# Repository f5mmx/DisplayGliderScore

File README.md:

Programme de gestion d'afficheur GliderScore
--------------------------------------------
Le but de ce dossier est de fournir les elements necessaires pour la réalisation d'un afficheur a brancher en sortie d'un PC avec GliderScore.

3 modules :
- 1 module de transmission en 2.4Ghz Canal 0 avec display Oled - Receive_Big
- 1 module de reception en 2.4 Ghz Canal 0 pour gestion GRAND afficheur segment diplay 7 digit - Transmit_all
_ 1 module de recpetion en 2.4 Ghz Canal 0 sur chrono avec afficheur Nokia 5119 - Small_Chrono

le Harware est basé sur des modules arduino nano + nrf24l01 + Large Driver 7 digit 

https://www.sparkfun.com/products/13279

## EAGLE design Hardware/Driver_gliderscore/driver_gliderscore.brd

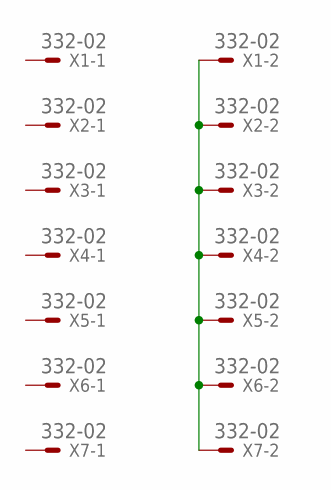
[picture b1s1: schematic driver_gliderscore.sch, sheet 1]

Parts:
X1, X2, X3, X4, X5, X6, X7: 332-02

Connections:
unnamed: X1.2, X2.2, X3.2, X4.2, X5.2, X6.2, X7.2

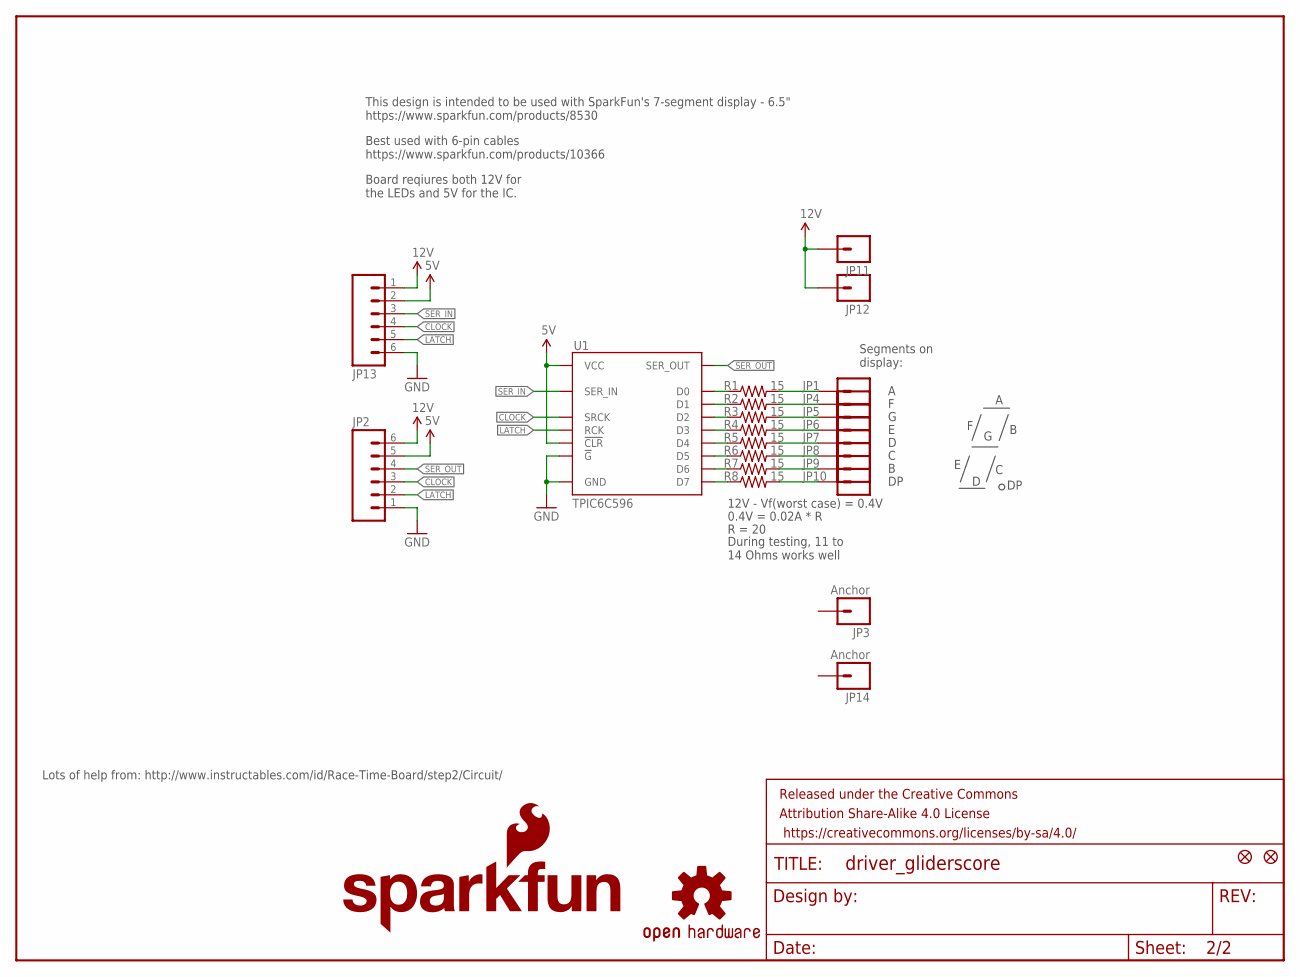
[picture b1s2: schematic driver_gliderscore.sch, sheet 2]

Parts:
FID1, FID2: FIDUCIAL1X2; FIDUCIAL-1X2
FRAME1: FRAME-LETTER; CREATIVE_COMMONS
JP1, JP4, JP5, JP6, JP7, JP8, JP9, JP10, JP11, JP12: M01PTH_LONGPAD; 1X01_LONGPAD
JP2, JP13: M06SMD; 1X06-SMD
JP3, JP14: Anchor; 1X01_LONGPAD
LOGO1: SFE_LOGO_NAME_FLAME.1_INCH; SFE_LOGO_NAME_FLAME_.1
LOGO2: OSHW-LOGOS; OSHW-LOGO-S
R1, R2, R3, R4, R5, R6, R7, R8: 15; 0603-RES
U1: TPIC6C596; SO016

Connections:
5V: JP2.5, JP13.2, U1.1 (VCC), U1.7 (!CLR)
12V: JP2.6, JP11.1, JP12.1, JP13.1
CLOCK: JP2.3, JP13.4, U1.15 (SRCK)
D0: R1.1, U1.3 (D0)
D1: R2.1, U1.4 (D1)
D2: R3.1, U1.5 (D2)
D3: R4.1, U1.6 (D3)
D4: R5.1, U1.11 (D4)
D5: R6.1, U1.12 (D5)
D6: R7.1, U1.13 (D6)
D7: R8.1, U1.14 (D7)
GND: JP2.1, JP13.6, U1.8 (!G), U1.16 (GND)
LATCH: JP2.2, JP13.5, U1.10 (RCK)
S0: JP1.1, R1.2
S1: JP4.1, R2.2
S2: JP5.1, R3.2
S3: JP6.1, R4.2
S4: JP7.1, R5.2
S5: JP8.1, R6.2
S6: JP9.1, R7.2
S7: JP10.1, R8.2
SER_IN: JP13.3, U1.2 (SER_IN)
SER_OUT: JP2.4, U1.9 (SER_OUT)

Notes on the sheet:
Lots of help from: http://www.instructables.com/id/Race-Time-Board/step2/Circuit/
Segments on display:
12V - Vf(worst case) = 0.4V
0.4V = 0.02A * R
R = 20
This design is intended to be used with SparkFun's 7-segment display - 6.5" https://www.sparkfun.com/products/8530
During testing, 11 to 14 Ohms works well
Best used with 6-pin cables https://www.sparkfun.com/products/10366
Board reqiures both 12V for the LEDs and 5V for the IC.

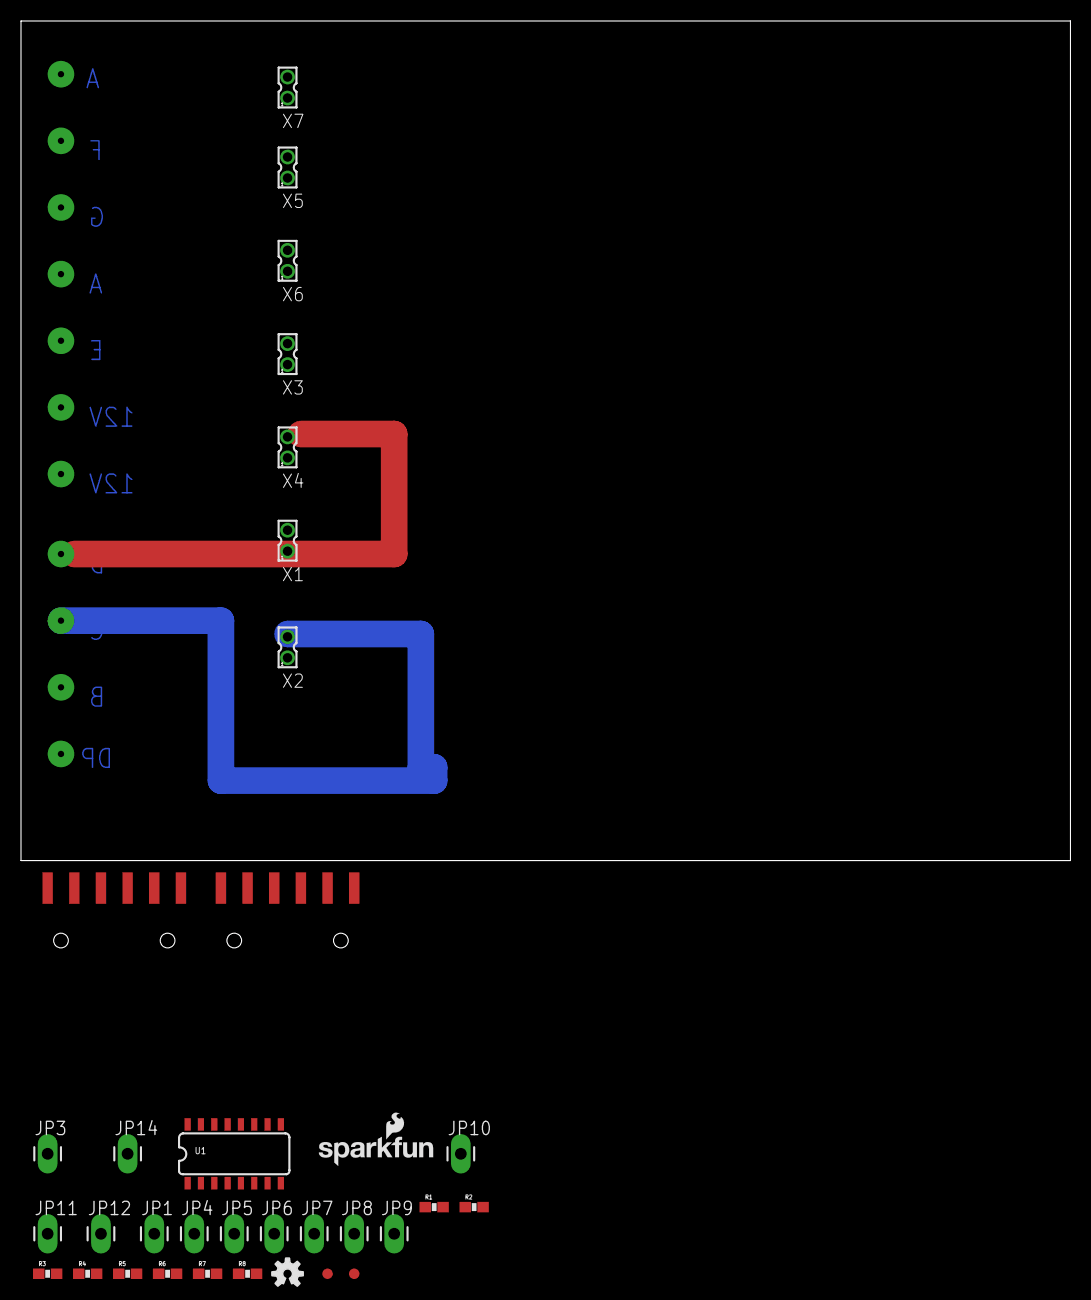
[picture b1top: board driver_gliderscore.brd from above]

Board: 2 copper layers, 100.0 x 80.0 mm, 35 parts (0 on the bottom side), 24 nets.

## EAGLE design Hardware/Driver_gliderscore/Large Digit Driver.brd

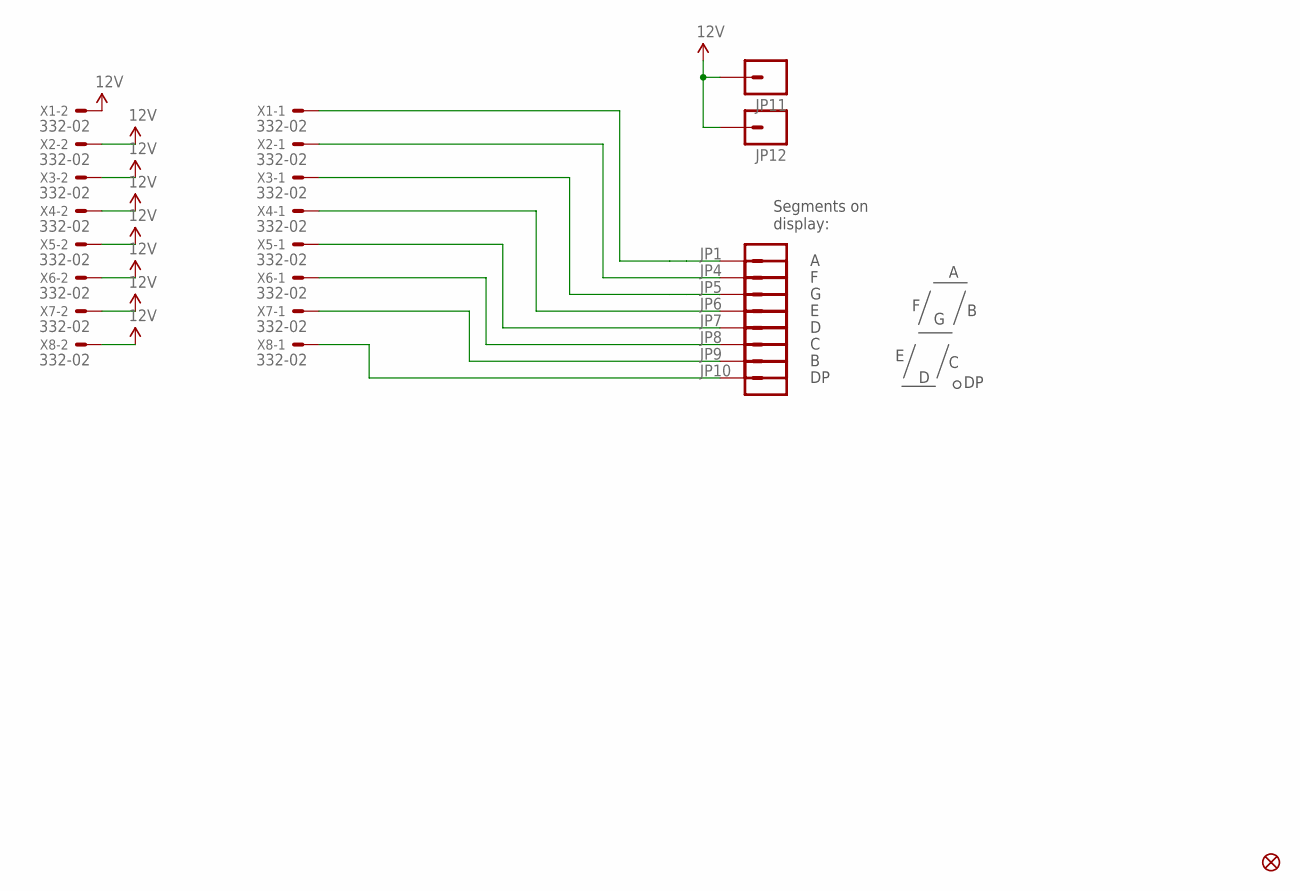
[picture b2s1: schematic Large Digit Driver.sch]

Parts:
FID2: FIDUCIAL1X2; FIDUCIAL-1X2
JP1, JP4, JP5, JP6, JP7, JP8, JP9, JP10, JP11, JP12: M01PTH_LONGPAD; 1X01_LONGPAD
X1, X2, X3, X4, X5, X6, X7, X8: 332-02

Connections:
12V: JP11.1, JP12.1, X1.2, X2.2, X3.2, X4.2, X5.2, X6.2, X7.2, X8.2
unnamed: JP9.1, X7.1
S0: JP1.1, X1.1
S1: JP4.1, X2.1
S2: JP5.1, X3.1
S3: JP6.1, X4.1
S4: JP7.1, X5.1
S5: JP8.1, X6.1
S7: JP10.1, X8.1

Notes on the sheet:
Segments on display:

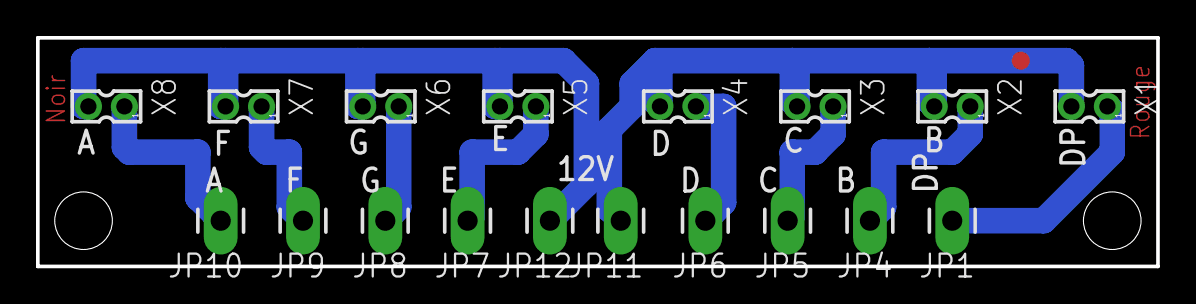
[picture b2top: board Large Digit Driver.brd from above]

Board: 2 copper layers, 62.2 x 12.7 mm, 19 parts (0 on the bottom side), 9 nets.

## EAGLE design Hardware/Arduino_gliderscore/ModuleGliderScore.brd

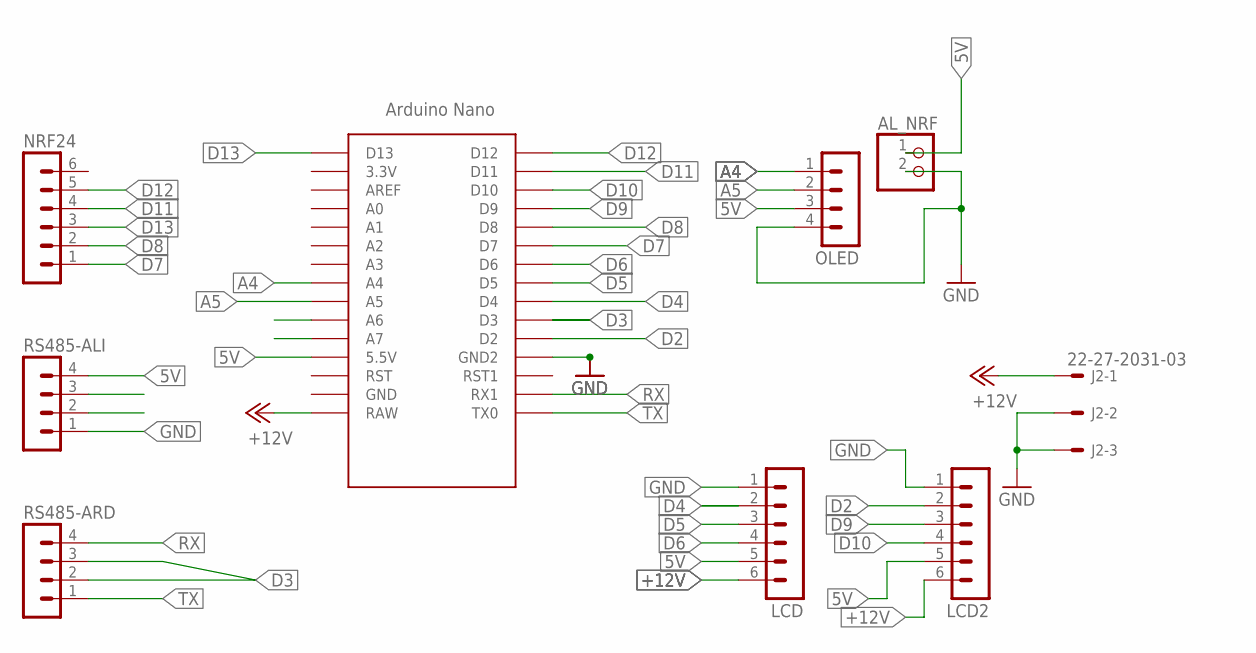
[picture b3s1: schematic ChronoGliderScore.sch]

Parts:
AL_NRF: PINHD-1X2; 1X02
J2: 22-27-2031-03; 6410-03
LCD, LCD2: MA06-1
NRF24: MA06-1
OLED: MA04-1
RS485-ALI, RS485-ARD: MA04-1
U$1: NANO

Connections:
5V: AL_NRF.1, LCD.5, LCD2.5, OLED.3, RS485-ALI.4, U$1.5V (5.5V)
+12V: J2.1, LCD.6, LCD2.6, U$1.RAW
A4: OLED.1, U$1.A4
A5: OLED.2, U$1.A5
A6-D: U$1.A6
A7-D: U$1.A7
D2: LCD2.2, U$1.D2
D3: RS485-ARD.2, RS485-ARD.3, U$1.D3
D4: LCD.2, U$1.D4
D5: LCD.3, U$1.D5
D6: LCD.4, U$1.D6
D7: NRF24.1, U$1.D7
D8: NRF24.2, U$1.D8
D9: LCD2.3, U$1.D9
D10: LCD2.4, U$1.D10
D11: NRF24.4, U$1.D11
D12: NRF24.5, U$1.D12
D13: NRF24.3, U$1.D13
GND: AL_NRF.2, J2.2, J2.3, LCD.1, LCD2.1, OLED.4, RS485-ALI.1, U$1.GND1 (GND2)
RX: RS485-ARD.4, U$1.RX1
TX: RS485-ARD.1, U$1.TX0

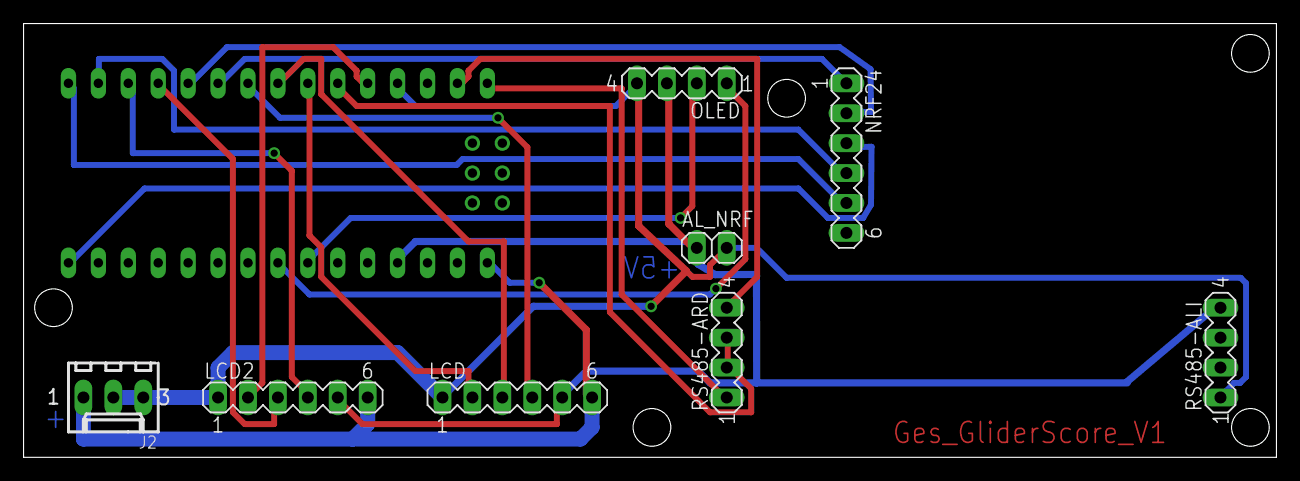
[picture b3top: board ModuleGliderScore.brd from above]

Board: 2 copper layers, 106.3 x 36.8 mm, 9 parts (0 on the bottom side), 19 nets.

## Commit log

2018-04-14 version iniatiale
2018-04-14 version initiale
2018-04-14 Fichiers Eagles
2018-11-10 Nouvelle version avec nouveau chrono autonome
2018-12-09 update du 9/12/2018
2018-12-24 Mise à jour du 24/12 avec rajout d'un chrono
2019-01-25 Version Janvier 2019 - 1.7

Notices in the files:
parts and their libraries:
SparkFun-Aesthetics: Licensing: CC v3.0 Share-Alike You are welcome to use this library for commercial purposes.
SparkFun-Aesthetics: Released under the Creative Commons Attribution Share-Alike 4.0 License
SparkFun-Aesthetics: https://creativecommons.org/licenses/by-sa/4.0
